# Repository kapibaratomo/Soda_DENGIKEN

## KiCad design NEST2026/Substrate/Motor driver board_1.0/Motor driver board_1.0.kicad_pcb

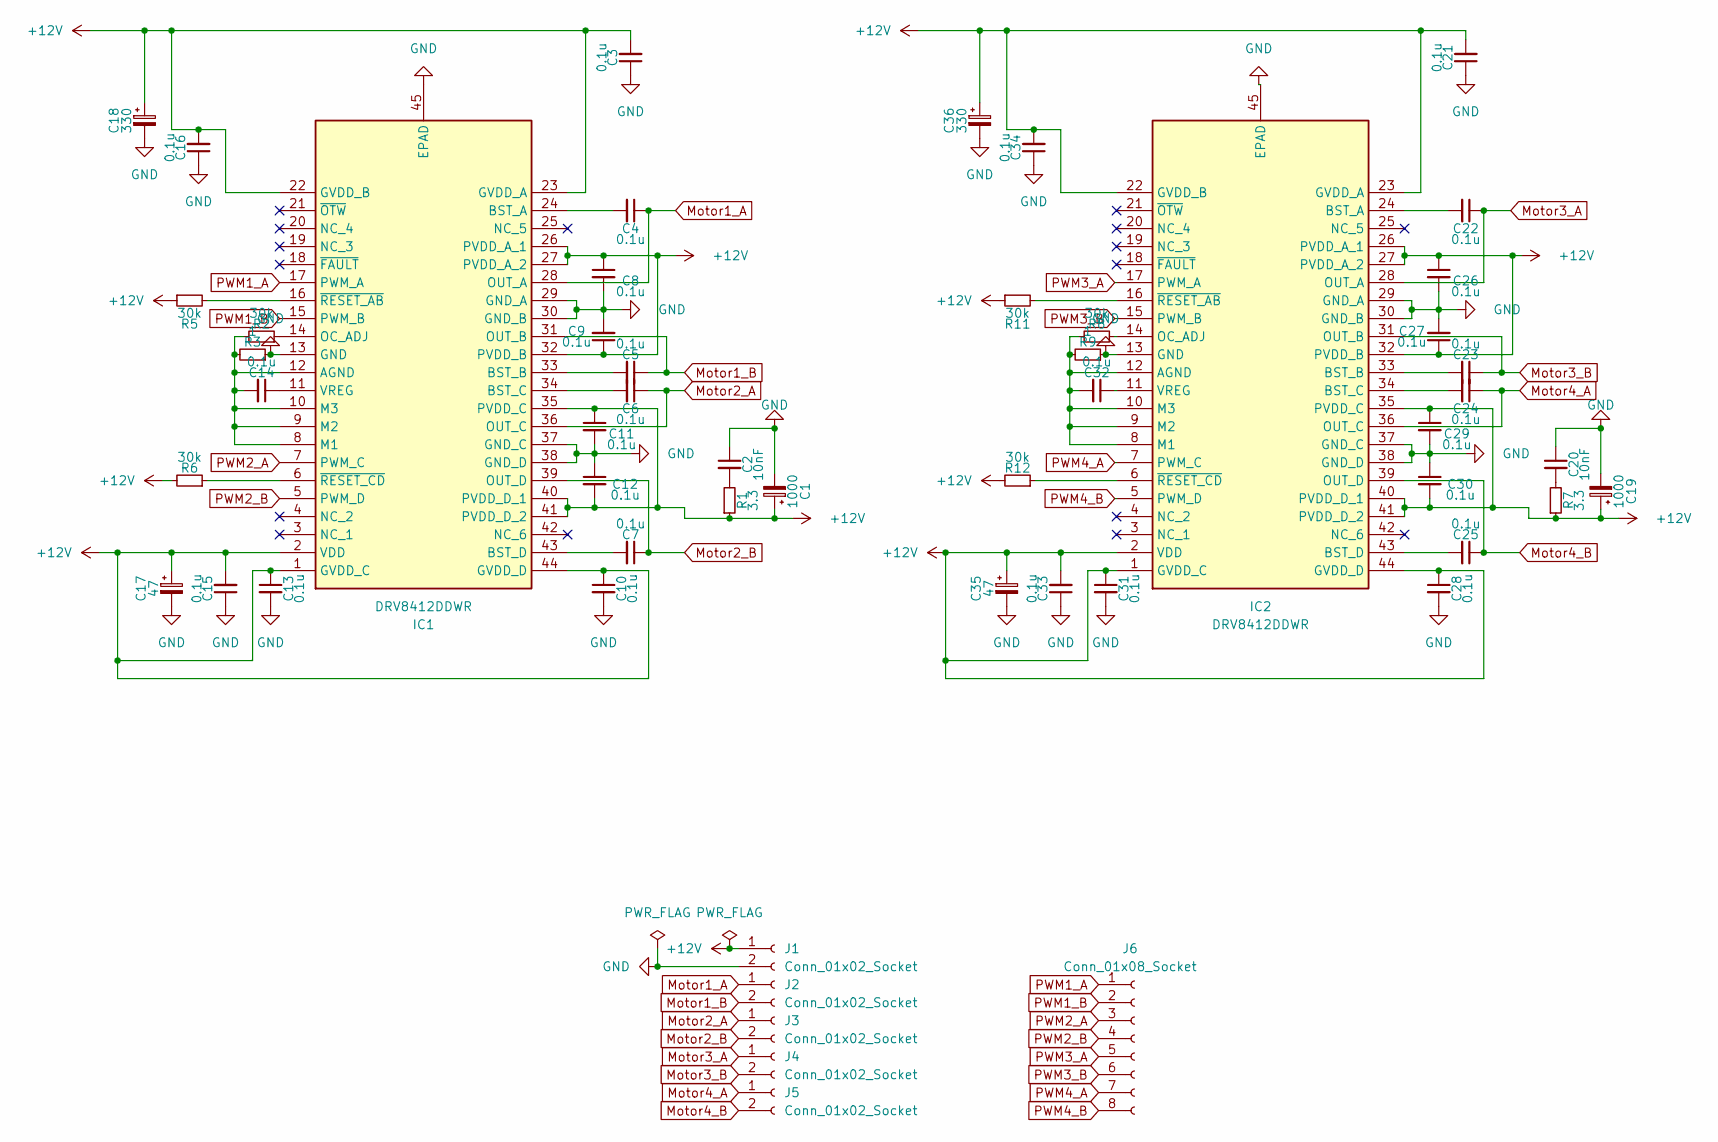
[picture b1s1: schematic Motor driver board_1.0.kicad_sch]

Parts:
C1, C19: 1000; CP_Radial_D10.0mm_P5.00mm
C2, C20: 10nF; C_0603_1608Metric
C3, C4, C5, C6, C7, C8, C9, C10, C11, C12, C13, C14, C15, C16, C21, C22, C23, C24, C25, C26, C27, C28, C29, C30, C31, C32, C33, C34: 0.1u; C_0603_1608Metric
C17, C35: 47; CP_Radial_D6.3mm_P2.50mm
C18, C36: 330; CP_Radial_D10.0mm_P5.00mm
IC1, IC2: DRV8412DDWR; HTSSOP-44-1EP_6.1x14mm_P0.635mm_EP5.2x14mm_Mask4.31x8.26mm; Manufacturer_Part_Number DRV8412DDWR
J1, J2, J3, J4, J5: Conn_01x02_Socket; JST_XH_S2B-XH-A_1x02_P2.50mm_Horizontal
J6: Conn_01x08_Socket; 0527450897
R1, R7: 3.3; R_0603_1608Metric
R2, R5, R6, R8, R11, R12: 30k; R_0603_1608Metric
R3, R9: 1; R_0603_1608Metric

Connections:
+12V: C1.1, C3.2, C8.1, C9.1, C10.1, C11.1, C12.2, C13.1, C15.2, C16.2, C17.1, C18.1, C19.1, C21.2, C26.1, C27.1, C28.1, C29.1, C30.2, C31.1, C33.2, C34.2, C35.1, C36.1, IC1.1 (GVDD_C), IC1.2 (VDD), IC1.22 (GVDD_B), IC1.23 (GVDD_A), IC1.26 (PVDD_A_1), IC1.27 (PVDD_A_2), IC1.32 (PVDD_B), IC1.35 (PVDD_C), IC1.40 (PVDD_D_1), IC1.41 (PVDD_D_2), IC1.44 (GVDD_D), IC2.1 (GVDD_C), IC2.2 (VDD), IC2.22 (GVDD_B), IC2.23 (GVDD_A), IC2.26 (PVDD_A_1), IC2.27 (PVDD_A_2), IC2.32 (PVDD_B), IC2.35 (PVDD_C), IC2.40 (PVDD_D_1), IC2.41 (PVDD_D_2), IC2.44 (GVDD_D), J1.1, R1.1, R5.1, R6.2, R7.1, R11.1, R12.2
GND: C1.2, C2.1, C3.1, C8.2, C9.2, C10.2, C11.2, C12.1, C13.2, C15.1, C16.1, C17.2, C18.2, C19.2, C20.1, C21.1, C26.2, C27.2, C28.2, C29.2, C30.1, C31.2, C33.1, C34.1, C35.2, C36.2, IC1.13 (GND), IC1.29 (GND_A), IC1.30 (GND_B), IC1.37 (GND_C), IC1.38 (GND_D), IC1.45 (EPAD), IC2.13 (GND), IC2.29 (GND_A), IC2.30 (GND_B), IC2.37 (GND_C), IC2.38 (GND_D), IC2.45 (EPAD), J1.2, R3.1, R9.1
Motor1_A: C4.1, IC1.28 (OUT_A), J2.1
Motor1_B: C5.1, IC1.31 (OUT_B), J2.2
Motor2_A: C6.1, IC1.36 (OUT_C), J3.1
Motor2_B: C7.1, IC1.39 (OUT_D), J3.2
Motor3_A: C22.1, IC2.28 (OUT_A), J4.1
Motor3_B: C23.1, IC2.31 (OUT_B), J4.2
Motor4_A: C24.1, IC2.36 (OUT_C), J5.1
Motor4_B: C25.1, IC2.39 (OUT_D), J5.2
unnamed: C2.2, R1.2
unnamed: C20.2, R7.2
unnamed: C14.2, IC1.8 (M1), IC1.9 (M2), IC1.10 (M3), IC1.12 (AGND), R2.2, R3.2
unnamed: C4.2, IC1.24 (BST_A)
unnamed: C5.2, IC1.33 (BST_B)
unnamed: C6.2, IC1.34 (BST_C)
unnamed: C7.2, IC1.43 (BST_D)
unnamed: IC1.14 (OC_ADJ), R2.1
unnamed: C14.1, IC1.11 (VREG)
unnamed: IC1.16 (~RESET_AB), R5.2
unnamed: IC1.6 (~RESET_CD), R6.1
unnamed: C32.2, IC2.8 (M1), IC2.9 (M2), IC2.10 (M3), IC2.12 (AGND), R8.1, R9.2
unnamed: C22.2, IC2.24 (BST_A)
unnamed: C23.2, IC2.33 (BST_B)
unnamed: C24.2, IC2.34 (BST_C)
unnamed: C25.2, IC2.43 (BST_D)
unnamed: IC2.14 (OC_ADJ), R8.2
unnamed: C32.1, IC2.11 (VREG)
unnamed: IC2.16 (~RESET_AB), R11.2
unnamed: IC2.6 (~RESET_CD), R12.1
PWM1_A: IC1.17 (PWM_A), J6.1
PWM1_B: IC1.15 (PWM_B), J6.2
PWM2_A: IC1.7 (PWM_C), J6.3
PWM2_B: IC1.5 (PWM_D), J6.4
PWM3_A: IC2.17 (PWM_A), J6.5
PWM3_B: IC2.15 (PWM_B), J6.6
PWM4_A: IC2.7 (PWM_C), J6.7
PWM4_B: IC2.5 (PWM_D), J6.8

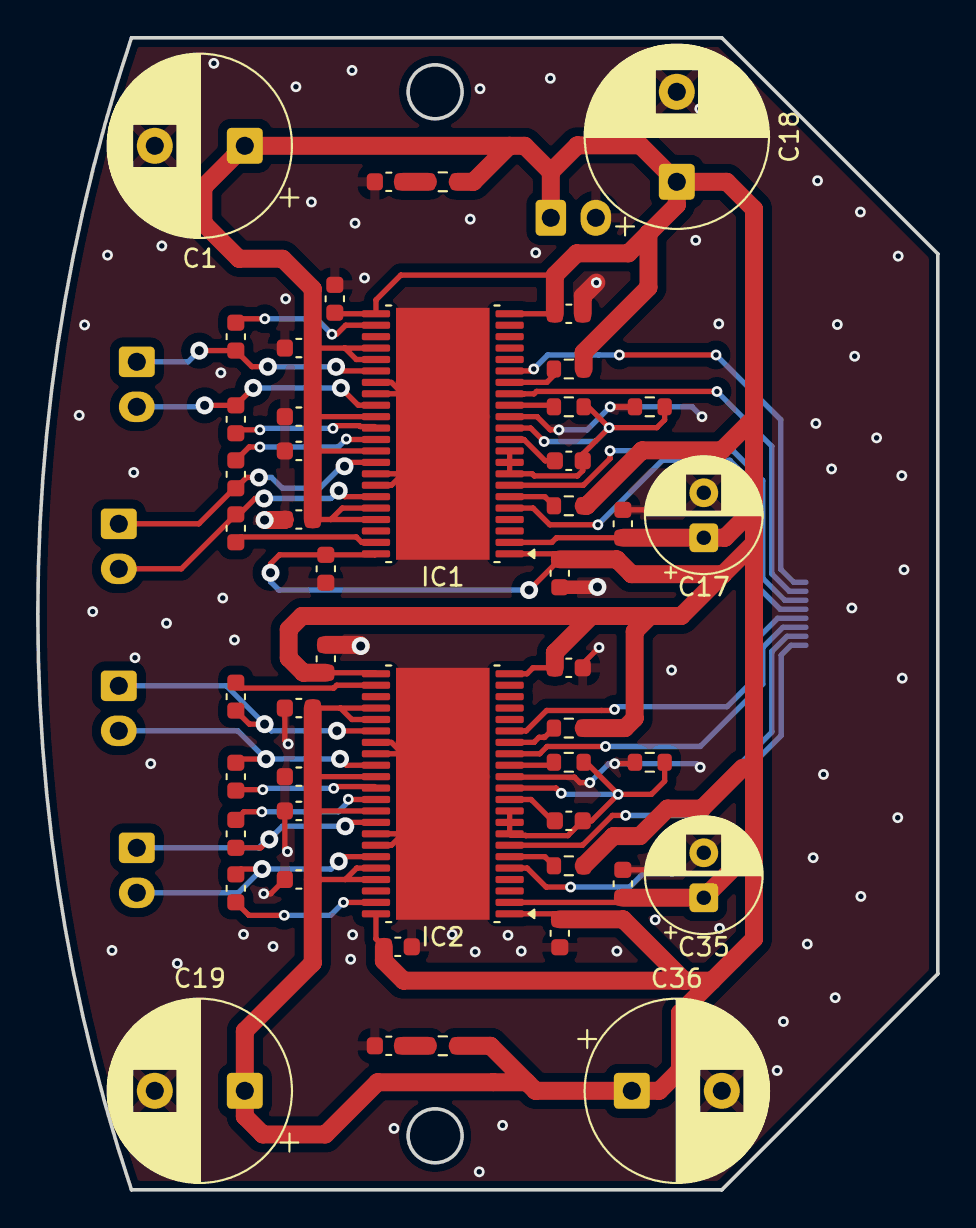
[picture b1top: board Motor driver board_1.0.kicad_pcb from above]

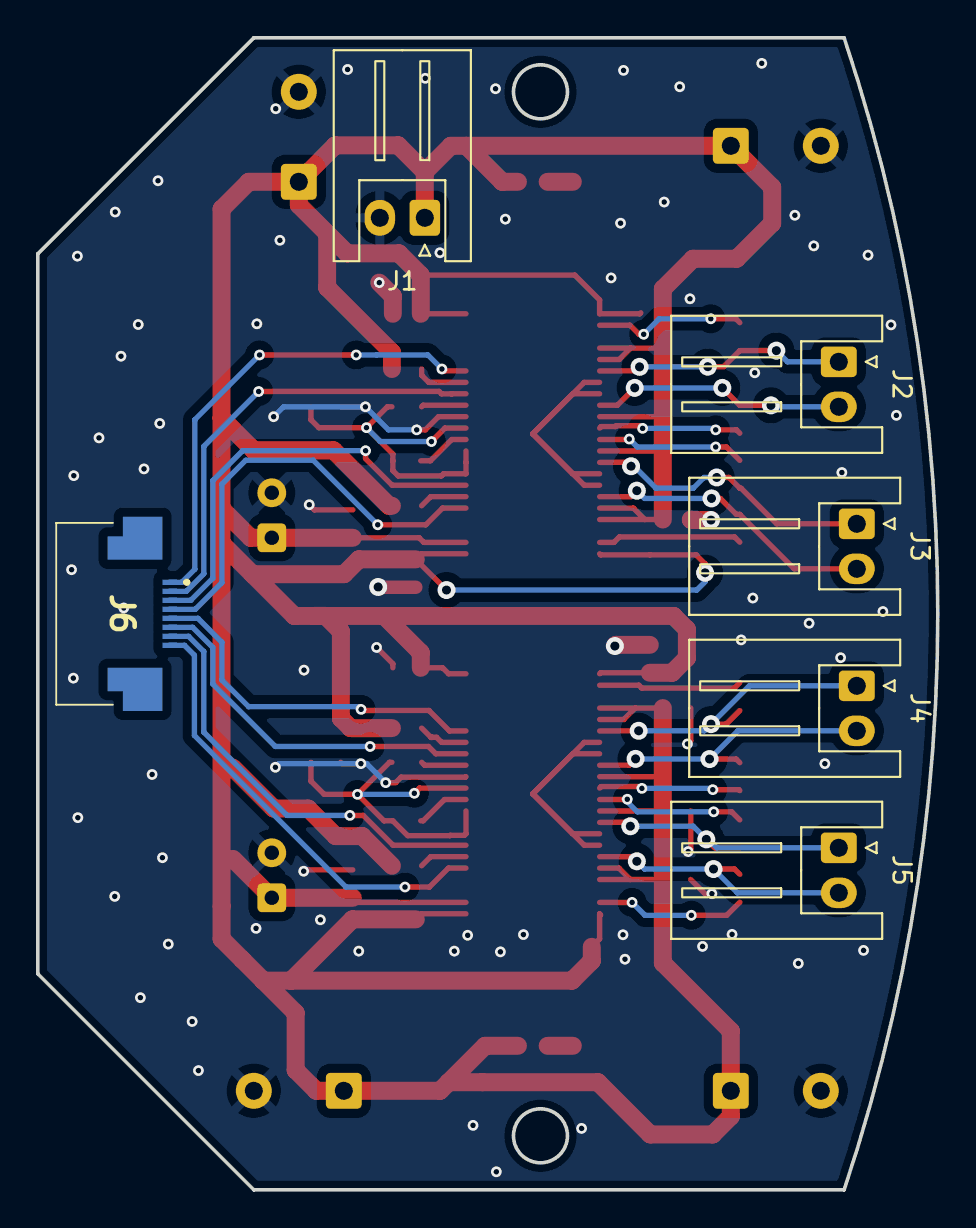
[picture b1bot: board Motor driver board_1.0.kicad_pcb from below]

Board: 2 copper layers, 50.0 x 64.0 mm, 54 parts (6 on the bottom side), 38 nets.

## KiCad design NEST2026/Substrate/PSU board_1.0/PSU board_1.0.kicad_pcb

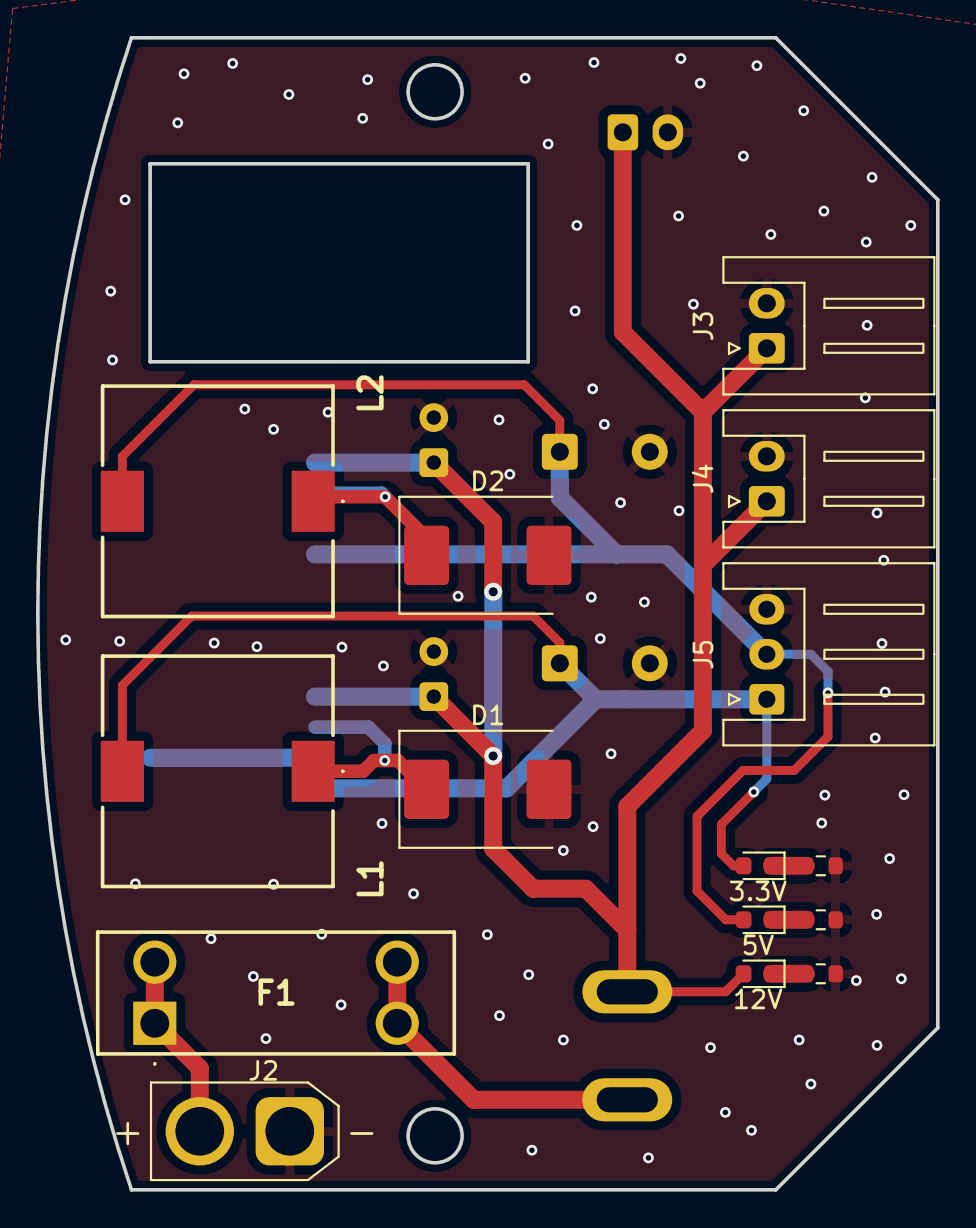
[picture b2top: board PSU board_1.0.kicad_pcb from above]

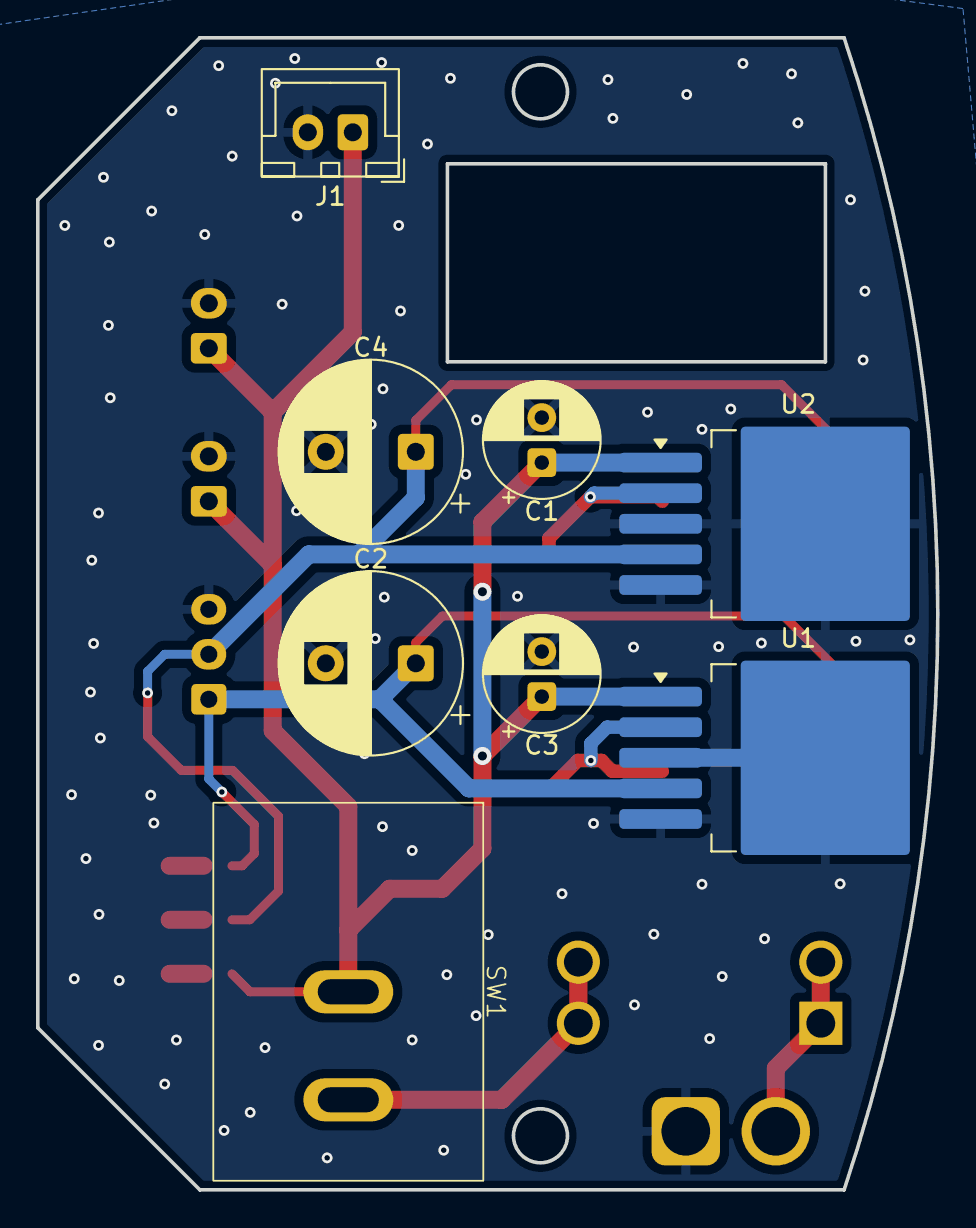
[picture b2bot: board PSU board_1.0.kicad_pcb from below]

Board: 2 copper layers, 50.0 x 64.0 mm, 23 parts (8 on the bottom side), 11 nets.

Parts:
3.3V, 5V, 12V: KT-0603W; LED_0603_1608Metric
C1, C3: 100u; CP_Radial_D6.3mm_P2.50mm
C2, C4: 1000u; CP_Radial_D10.0mm_P5.00mm
D1, D2: MBRS360T3G; D_SMC
F1: Fuse; 355715
J1: 電圧計; JST_XH_B2B-XH-A_1x02_P2.50mm_Vertical
J2: Conn_01x02_Socket; AMASS_XT30U-M_1x02_P5.0mm_Vertical
J3: Motor driver board; JST_XH_S2B-XH-A_1x02_P2.50mm_Horizontal
J4: kicker board; JST_XH_S2B-XH-A_1x02_P2.50mm_Horizontal
J5: Main board; JST_XH_S3B-XH-A_1x03_P2.50mm_Horizontal
L1, L2: 100; PA4309104NLT
R1: 1k; R_0603_1608Metric
R2: 220; R_0603_1608Metric
R3: 49.9; R_0603_1608Metric
SW1: SW_SPST; DS-850K-S
U1: LM2576S-3.3; TO-263-5_TabPin3
U2: LM2576S-5; TO-263-5_TabPin3

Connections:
+3.3V: 3.3V.2 (A), C2.1, J5.1, L1.2, U1.4 (FB)
+5V: 5V.2 (A), C4.1, J5.2, L2.2, U2.4 (FB)
+12V: 12V.2 (A), C1.1, C3.1, J1.1, J3.1, J4.1, SW1.2 (B), U1.1 (VIN), U2.1 (VIN)
GND: C1.2, C2.2, C3.2, C4.2, D1.2 (A), D2.2 (A), J1.2, J2.1, J3.2, J4.2, J5.3, R1.1, R2.1, R3.1, U1.3 (GND), U1.5 (~ON/OFF), U2.3 (GND), U2.5 (~ON/OFF)
unnamed: D1.1 (K), L1.1, U1.2 (OUT)
unnamed: D2.1 (K), L2.1, U2.2 (OUT)
unnamed: 12V.1 (K), R1.2
unnamed: 5V.1 (K), R2.2
unnamed: 3.3V.1 (K), R3.2
unnamed: F1.1, J2.2
unnamed: F1.2, SW1.1 (A)

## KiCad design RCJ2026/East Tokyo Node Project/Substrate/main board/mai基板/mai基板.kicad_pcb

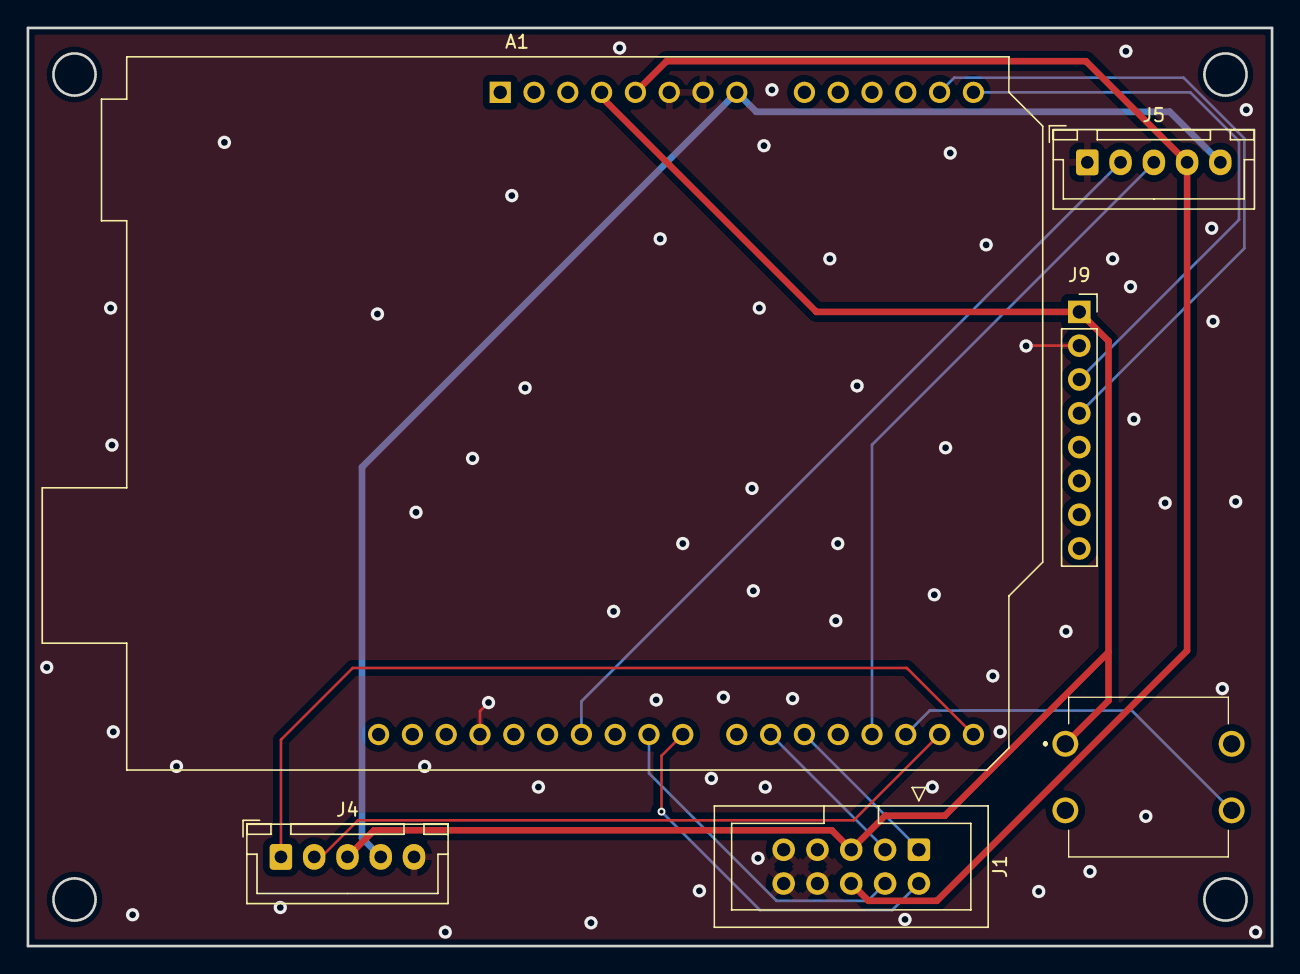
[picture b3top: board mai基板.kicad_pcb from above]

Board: 2 copper layers, 93.5 x 69.0 mm, 6 parts (0 on the bottom side), 15 nets.

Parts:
A1: Arduino_UNO_R3
J1: Conn_02x05_Odd_Even; IDC-Header_2x05_P2.54mm_Vertical
J4, J5: Conn_01x05_Pin; JST_XH_B5B-XH-A_1x05_P2.50mm_Vertical
J9: Conn_01x08_Pin; PinSocket_1x08_P2.54mm_Vertical
S**: TVGP01G73BB

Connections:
+3.3V: A1.4 (3V3), J1.5, J4.3, J9.1, S**.1
+5V: A1.5 (+5V), J1.6, J5.4
+9V: A1.8 (VIN), J4.4, J5.5
D2: A1.17 (D2), S**.4
GND: A1.6 (GND), A1.7 (GND), A1.29 (GND), J1.7, J1.8, J1.9, J1.10, J4.5, J5.1, J9.2
IN1: A1.18 (D3), J5.3
PWM1: A1.20 (D5), J1.1
PWM2: A1.21 (D6), J1.3
PWM3: A1.23 (D8), J1.2
PWM4: A1.24 (D9), J1.4
PWM5: A1.26 (D11), J5.2
RX: A1.15 (D0/RX), J4.1
SCL: A1.14 (SCL/A5), J9.3
SDA: A1.13 (SDA/A4), J9.4
TX: A1.16 (D1/TX), J4.2

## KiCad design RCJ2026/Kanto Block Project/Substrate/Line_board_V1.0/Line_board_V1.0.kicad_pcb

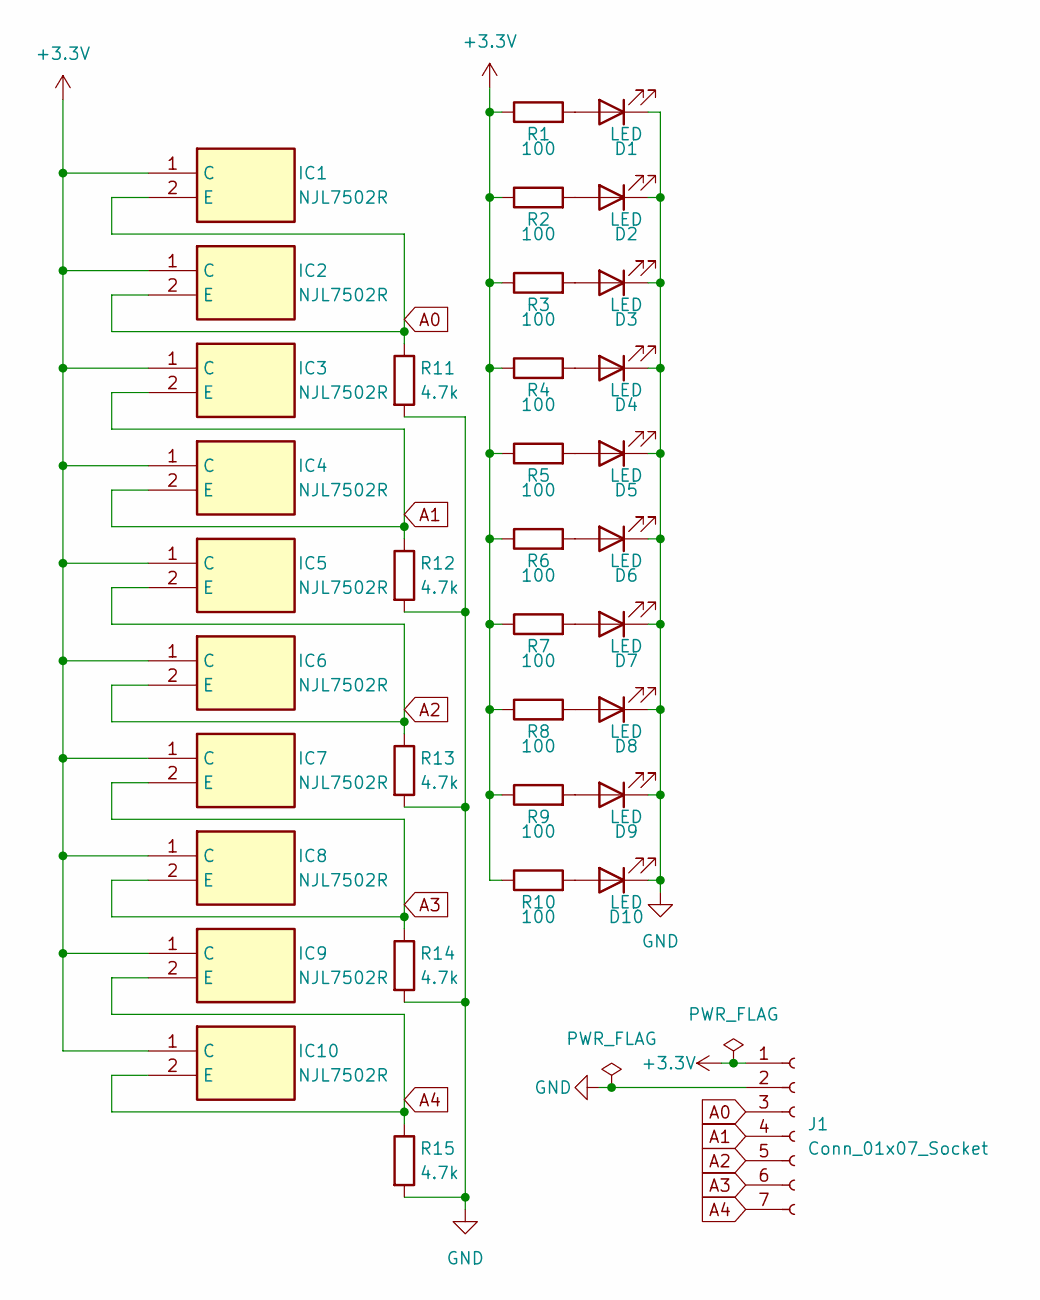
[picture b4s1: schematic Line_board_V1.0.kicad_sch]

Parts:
D1, D2, D3, D4, D5, D6, D7, D8, D9, D10: LED; LED_0603_1608Metric
IC1, IC2, IC3, IC4, IC5, IC6, IC7, IC8, IC9, IC10: NJL7502R; Manufacturer_Part_Number NJL7502R
J1: Conn_01x07_Socket; JST_XH_B7B-XH-A_1x07_P2.50mm_Vertical
R1, R2, R3, R4, R5, R6, R7, R8, R9, R10: 100; R_0603_1608Metric
R11, R12, R13, R14, R15: 4.7k; R_0603_1608Metric

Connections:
+3.3V: IC1.1 (C), IC2.1 (C), IC3.1 (C), IC4.1 (C), IC5.1 (C), IC6.1 (C), IC7.1 (C), IC8.1 (C), IC9.1 (C), IC10.1 (C), J1.1, R1.1, R2.1, R3.1, R4.1, R5.1, R6.1, R7.1, R8.1, R9.1, R10.1
A0: IC1.2 (E), IC2.2 (E), J1.3, R11.1
A1: IC3.2 (E), IC4.2 (E), J1.4, R12.1
A2: IC5.2 (E), IC6.2 (E), J1.5, R13.1
A3: IC7.2 (E), IC8.2 (E), J1.6, R14.1
A4: IC9.2 (E), IC10.2 (E), J1.7, R15.1
GND: D1.1 (K), D2.1 (K), D3.1 (K), D4.1 (K), D5.1 (K), D6.1 (K), D7.1 (K), D8.1 (K), D9.1 (K), D10.1 (K), J1.2, R11.2, R12.2, R13.2, R14.2, R15.2
unnamed: D1.2 (A), R1.2
unnamed: D2.2 (A), R2.2
unnamed: D3.2 (A), R3.2
unnamed: D4.2 (A), R4.2
unnamed: D5.2 (A), R5.2
unnamed: D6.2 (A), R6.2
unnamed: D7.2 (A), R7.2
unnamed: D8.2 (A), R8.2
unnamed: D9.2 (A), R9.2
unnamed: D10.2 (A), R10.2

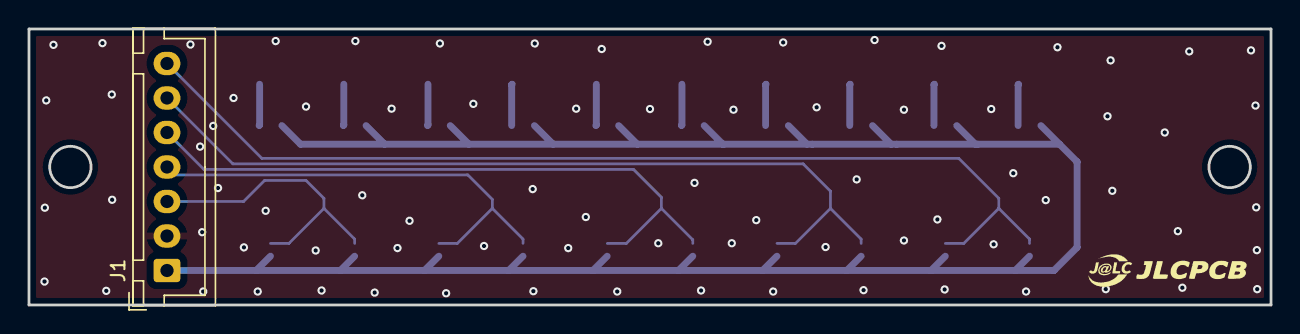
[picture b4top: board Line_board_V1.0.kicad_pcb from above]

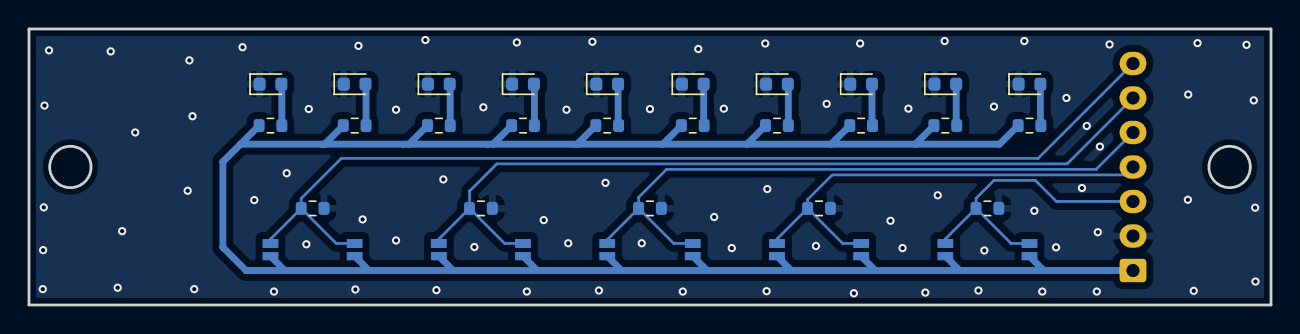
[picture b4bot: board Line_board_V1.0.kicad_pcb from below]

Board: 2 copper layers, 90.0 x 20.0 mm, 36 parts (35 on the bottom side), 17 nets.

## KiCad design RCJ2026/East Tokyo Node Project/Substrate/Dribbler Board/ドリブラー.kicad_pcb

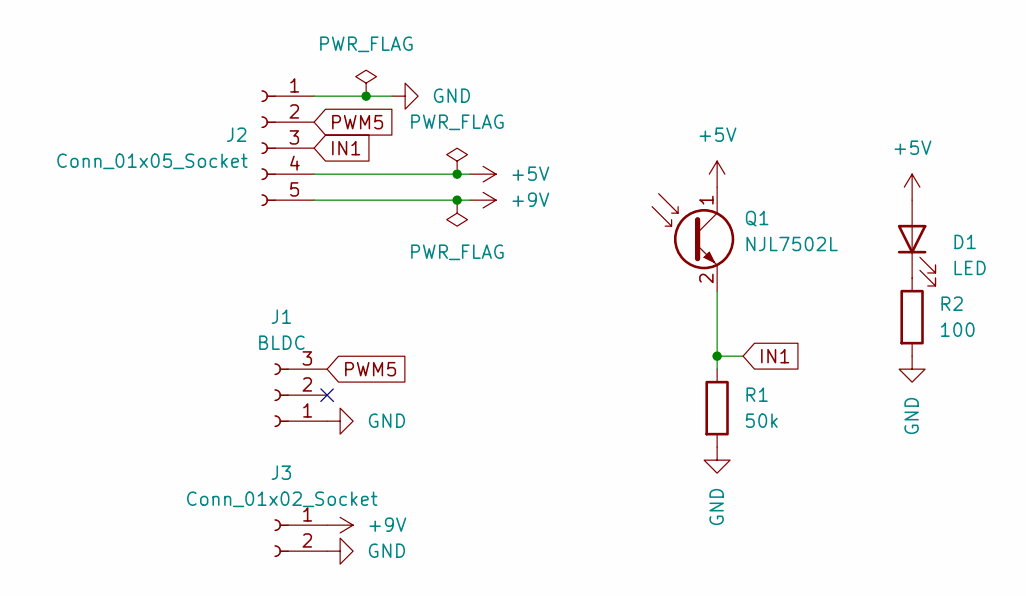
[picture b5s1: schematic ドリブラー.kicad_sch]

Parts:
D1: LED; LED_D5.0mm_Clear
J1: BLDC; JST_XH_B3B-XH-A_1x03_P2.50mm_Vertical
J2: Conn_01x05_Socket; JST_XH_B5B-XH-A_1x05_P2.50mm_Vertical
J3: Conn_01x02_Socket; AMASS_XT60-M_1x02_P7.20mm_Vertical
Q1: NJL7502L
R1: 50k; R_0603_1608Metric
R2: 100; R_0603_1608Metric

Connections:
+5V: D1.2 (A), J2.4, Q1.1 (C)
+9V: J2.5, J3.1
GND: J1.1, J2.1, J3.2, R1.2, R2.2
IN1: J2.3, Q1.2 (E), R1.1
unnamed: D1.1 (K), R2.1
PWM5: J1.3, J2.2

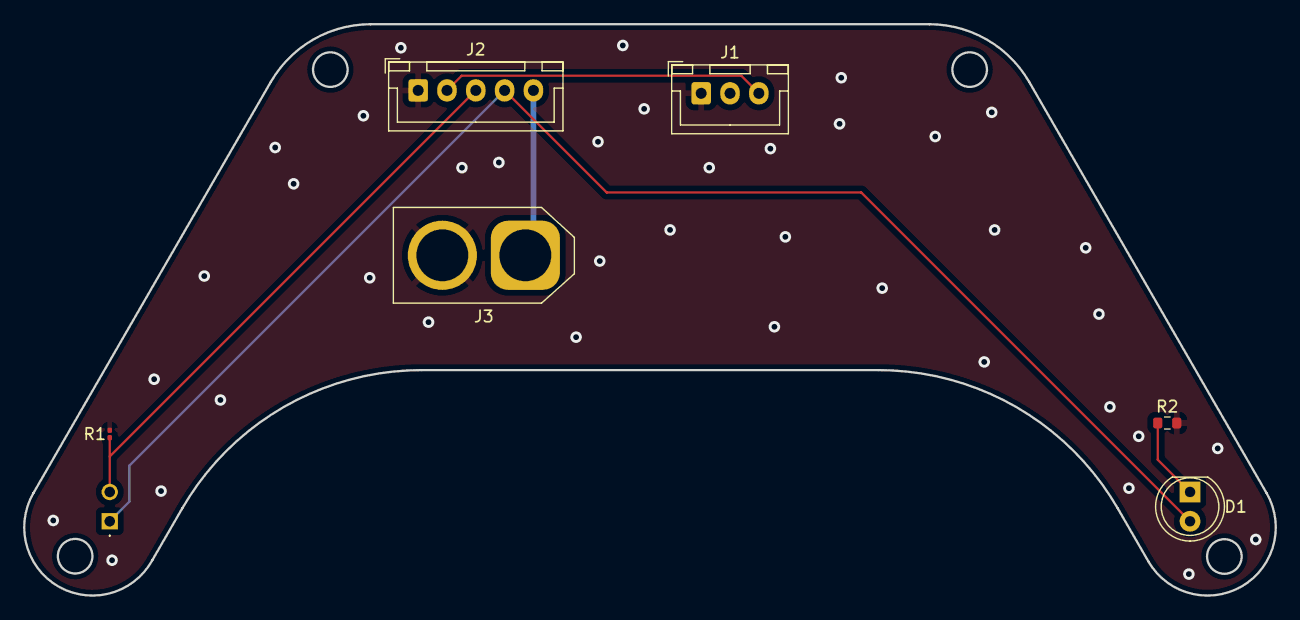
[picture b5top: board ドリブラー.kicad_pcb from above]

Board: 2 copper layers, 108.6 x 49.6 mm, 7 parts (0 on the bottom side), 6 nets.

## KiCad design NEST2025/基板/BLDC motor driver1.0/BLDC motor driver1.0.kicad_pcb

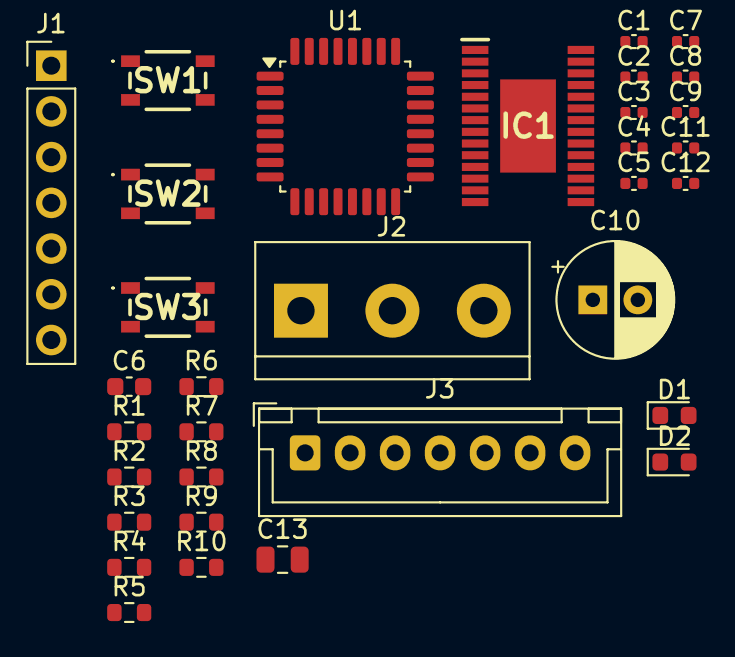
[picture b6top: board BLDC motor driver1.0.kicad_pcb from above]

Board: 2 copper layers, 33 parts (0 on the bottom side), 33 nets, no tracks yet.

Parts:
C1, C3, C5, C7, C9, C11, C12: 0.1; C_0402_1005Metric
C2, C8: 0.01; C_0402_1005Metric
C4: 1; C_0402_1005Metric
C6: 4.7; C_0603_1608Metric
C10: 100; CP_Radial_D6.3mm_P2.50mm
C13: 0.47; C_0805_2012Metric
D1: UI_LED; LED_0603_1608Metric
D2: 3.3V_LED; LED_0603_1608Metric
IC1: DRV8313PWPR
J1: PC; PinHeader_1x07_P2.54mm_Vertical
J2: BLDC motor; TerminalBlock_bornier-3_P5.08mm
J3: Main; JST_XH_B7B-XH-A_1x07_P2.50mm_Vertical
R1, R2, R3, R4, R5, R6, R7, R8, R9, R10: 10k; R_0603_1608Metric
SW1: NRST; SKRPABE010
SW2: BOOT; SKRPABE010
SW3: UI_SW; SKRPABE010
U1: STM32F303K8Tx; LQFP-32_7x7mm_P0.8mm

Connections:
+3.3V: C1.1, C2.1, C3.1, C4.1, C5.1, C6.1, D2.2 (A), J1.1, J3.2, R4.1, R5.1, R6.1, R7.1, R8.1, R9.1, SW2.1, SW3.1, U1.1 (VDD), U1.5 (VDDA), U1.17 (VDD)
+9V: C9.1, C10.1, C11.2, C12.1, IC1.4 (VM_1), IC1.11 (VM_2), J3.1
BOOT: R1.1, SW2.2, U1.31 (BOOT0)
EN1: IC1.26 (EN1), R7.2
EN2: IC1.24 (EN2), R8.2
EN3: IC1.22 (EN3), R9.2
GND: C1.2, C2.2, C3.2, C4.2, C5.2, C6.2, C7.2, C9.2, C10.2, C12.2, C13.2, IC1.6 (PGND1), IC1.7 (PGND2), IC1.10 (PGND3), IC1.12 (COMPP), IC1.13 (COMPN), IC1.14 (GND_1), IC1.19 (NCOMPO), IC1.20 (GND_2), IC1.21 (NC), IC1.28 (GND_3), IC1.29 (PowerPAD), J1.3, J3.3, R1.2, R2.2, R3.2, R10.2, SW1.1, U1.16 (VSS), U1.32 (VSS)
NRST: C7.1, J1.5, SW1.2, U1.4 (NRST)
unnamed: D1.1 (K), R2.1
unnamed: D2.1 (K), R3.1
unnamed: C8.2, IC1.2 (CPH)
unnamed: C8.1, IC1.1 (CPL)
unnamed: C13.1, IC1.15 (V3P3)
unnamed: C11.1, IC1.3 (VCP)
OUT_A: IC1.5 (OUT1), J2.1
OUT_B: IC1.8 (OUT2), J2.2
OUT_C: IC1.9 (OUT3), J2.3
PWM_A: IC1.27 (IN1), U1.6 (PA0)
PWM_B: IC1.25 (IN2), U1.7 (PA1)
PWM_C: IC1.23 (IN3), U1.8 (PA2)
SPI_CS: J3.7, U1.10 (PA4)
SPI_MISO: J3.5, U1.12 (PA6)
SPI_MOSI: J3.6, U1.13 (PA7)
SPI_SCK: J3.4, U1.11 (PA5)
SWCLK: J1.2, U1.24 (PA14)
SWDIO: J1.4, U1.23 (PA13)
UI_LED: D1.2 (A), U1.14 (PB0)
UI_SW: R10.1, SW3.2, U1.28 (PB5)
USART1_RX: J1.7, U1.20 (PA10)
USART1_TX: J1.6, U1.19 (PA9)
nFAULT: IC1.18 (NFAULT), R4.2
nRESET: IC1.16 (NRESET), R6.2
nSLEEP: IC1.17 (NSLEEP), R5.2

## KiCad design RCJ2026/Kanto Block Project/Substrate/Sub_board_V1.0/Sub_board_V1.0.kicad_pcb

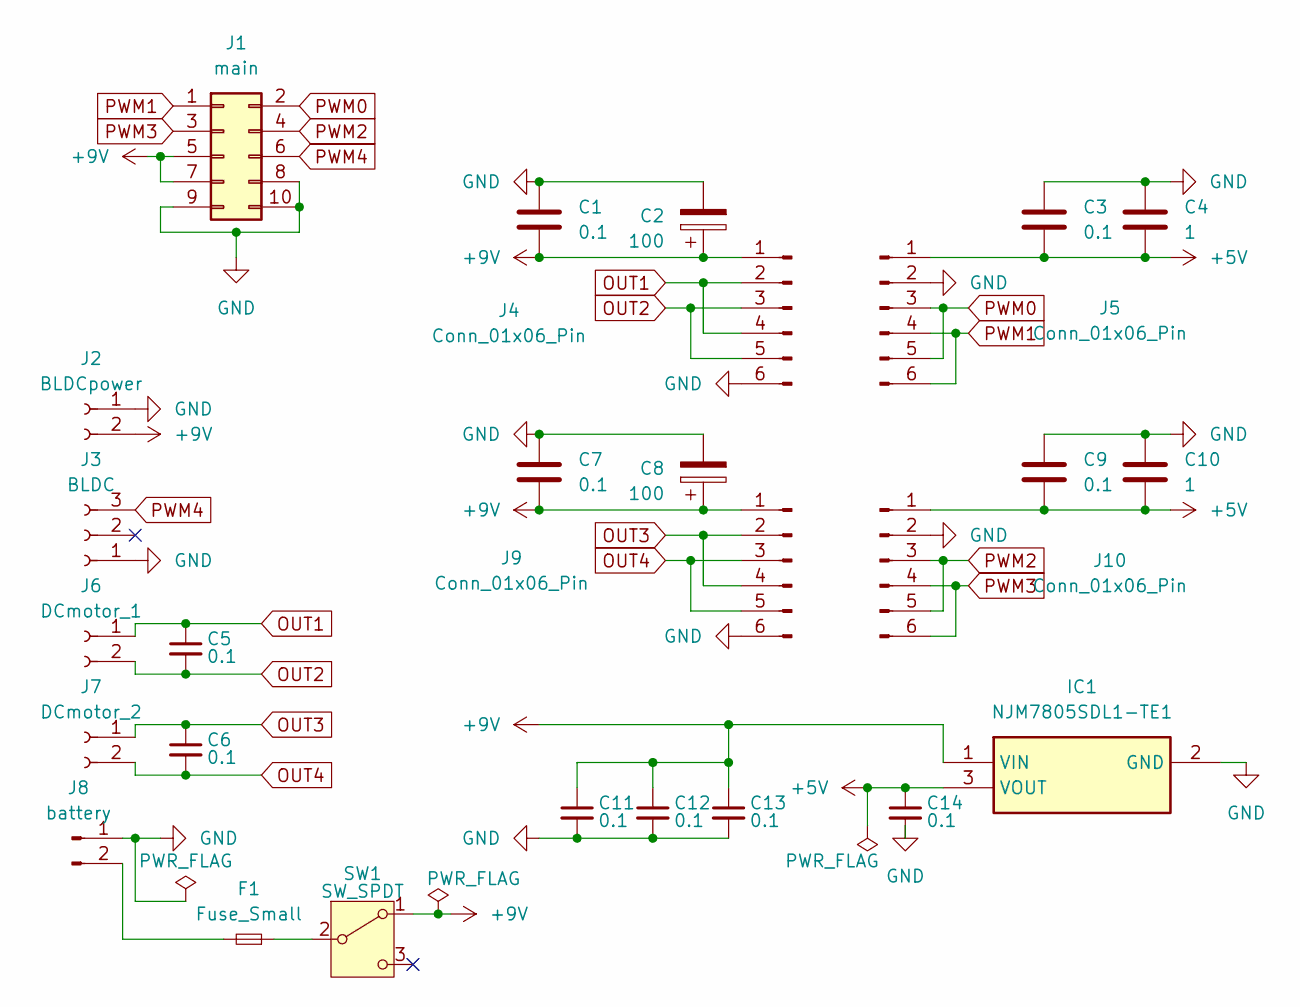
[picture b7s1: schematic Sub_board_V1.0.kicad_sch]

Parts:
C1, C3, C5, C6, C7, C9, C11, C12, C13, C14: 0.1; C_0603_1608Metric
C2, C8: 100; C_Radial_D6.3mm_H7.0mm_P2.50mm
C4, C10: 1; C_0603_1608Metric
F1: Fuse_Small; 355715
IC1: NJM7805SDL1-TE1; NJM7805SDL1TE1; Manufacturer_Part_Number NJM7805SDL1-TE1; Mouser Part Number 513-NJM7805SDL1-TE1
J1: main; IDC-Header_2x05_P2.54mm_Vertical
J2: BLDCpower; AMASS_XT60PW-F_1x02_P7.20mm_Horizontal
J3: BLDC; JST_XH_B3B-XH-A_1x03_P2.50mm_Vertical
J4, J5, J9, J10: Conn_01x06_Pin; PinSocket_1x06_P2.54mm_Vertical
J6: DCmotor_1; JST_XH_B2B-XH-A_1x02_P2.50mm_Vertical
J7: DCmotor_2; JST_XH_B2B-XH-A_1x02_P2.50mm_Vertical
J8: battery; AMASS_XT30PW-M_1x02_P2.50mm_Horizontal
SW1: SW_SPDT; 2MS1T2B4M2QES

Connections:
+5V: C3.2, C4.2, C9.2, C10.2, C14.1, IC1.3 (VOUT), J5.1, J10.1
+9V: C1.2, C2.1, C7.2, C8.1, C11.1, C12.1, C13.1, IC1.1 (VIN), J1.5, J1.7, J2.2, J4.1, J9.1, SW1.1 (A)
GND: C1.1, C2.2, C3.1, C4.1, C7.1, C8.2, C9.1, C10.1, C11.2, C12.2, C13.2, C14.2, IC1.2 (GND), J1.8, J1.9, J1.10, J2.1, J3.1, J4.6, J5.2, J8.1, J9.6, J10.2
unnamed: F1.2, J8.2
unnamed: F1.1, SW1.2 (B)
OUT1: C5.1, J4.2, J4.4, J6.1
OUT2: C5.2, J4.3, J4.5, J6.2
OUT3: C6.1, J7.1, J9.2, J9.4
OUT4: C6.2, J7.2, J9.3, J9.5
PWM0: J1.2, J5.3, J5.5
PWM1: J1.1, J5.4, J5.6
PWM2: J1.4, J10.3, J10.5
PWM3: J1.3, J10.4, J10.6
PWM4: J1.6, J3.3

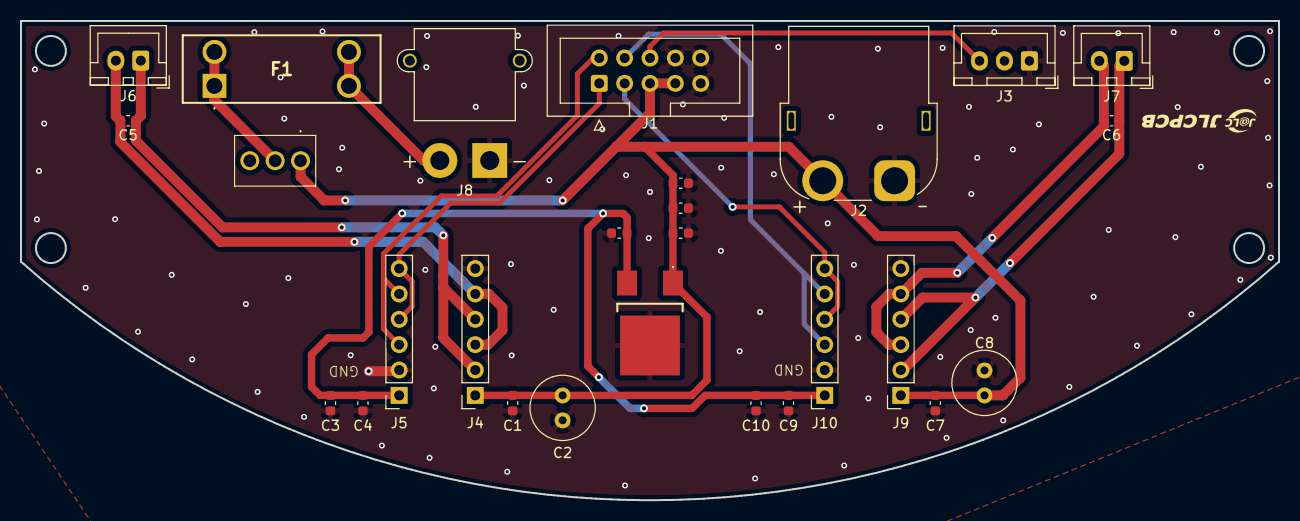
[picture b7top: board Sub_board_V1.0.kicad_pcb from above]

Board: 2 copper layers, 126.0 x 48.0 mm, 27 parts (0 on the bottom side), 14 nets.
